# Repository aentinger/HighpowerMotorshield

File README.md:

💾 Highpower Motorshield
========================

# 📸 Image

# 📂 Description

The Highpower Motorshield facilitates the control of a highpower DC (direct current) motor (18 V / 46 A) with an Arduino. The shield also permits the measurement of the motor current. For a quick and easy start, an open source Arduino library with sample programs is available.

**Features**

* Control of a normal direct current motor
* Supply voltage range: 7 to 18 Volts
* Can be used with 2S, 3S and 4S LiPo-battery
* High performance: Maximum continuous output current: 46 A
* Motor drivers are protected against short circuiting (to ground/supply), overheating, overvoltage and undervoltage
* Current measurement of the motor current
* Arduino Library with example programs is available on GitHub

# 🎥 [Video](images/highpower_motorshield_demo.mp4)

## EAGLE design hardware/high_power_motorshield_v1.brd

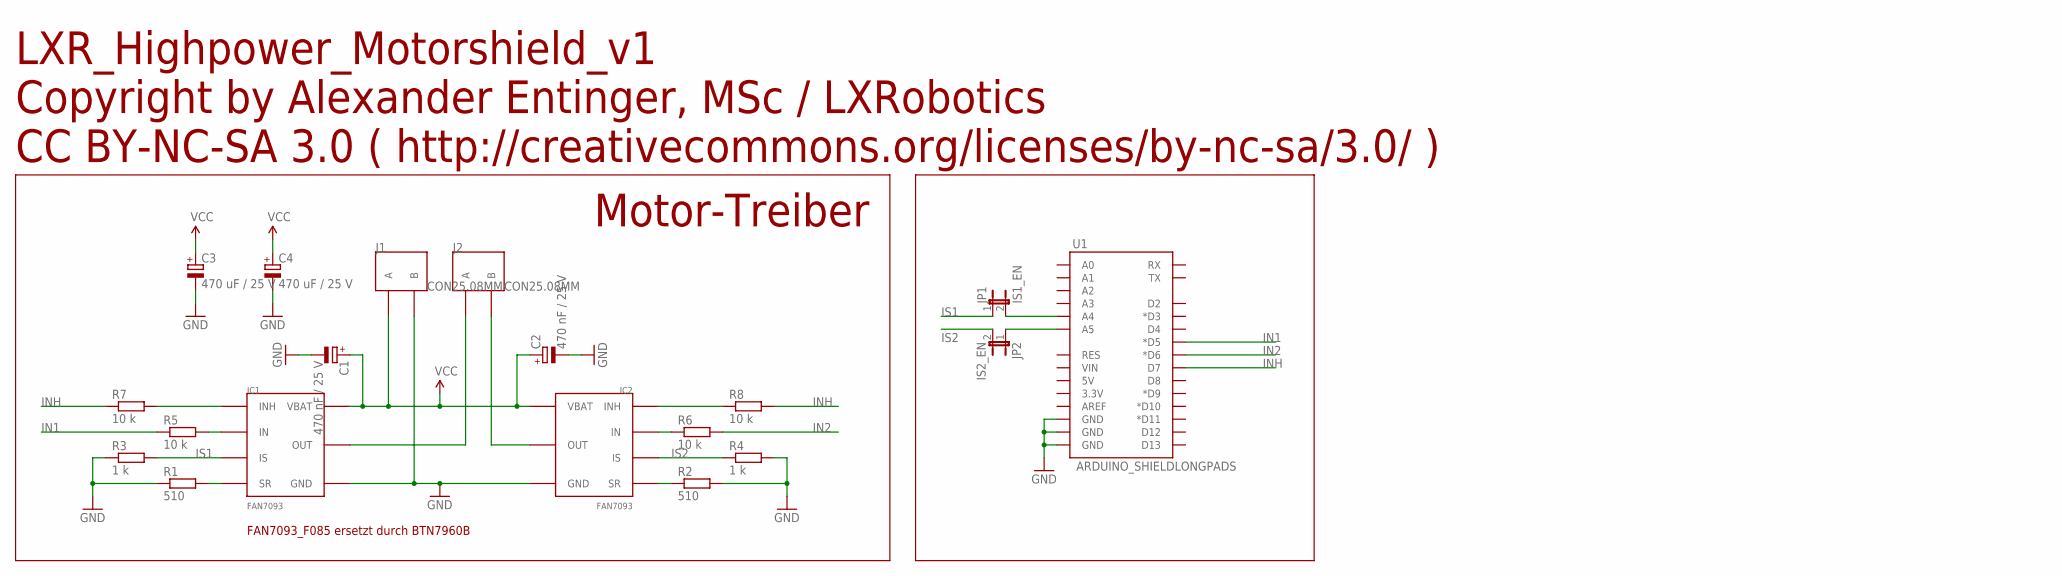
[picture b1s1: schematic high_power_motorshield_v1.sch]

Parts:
C1, C2: 470 nF / 25 V; KEMET_A
C3, C4: 470 uF / 25 V; E5-10,5
IC1, IC2: FAN7093; TO263-7L
J1, J2: CON25.08MM; CON2_SCHRAUBKLEMME
JP1: IS1_EN; JP1
JP2: IS2_EN; JP1
R1, R2: 510; R0805
R3, R4: 1 k; R0805
R5, R6, R7, R8: 10 k; R0805
U1: ARDUINO_SHIELDLONGPADS; DUEMILANOVE_SHIELD_LONGPADS

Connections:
GND: C1.CATHODE (-), C2.CATHODE (-), C3.-, C4.-, IC1.GND, IC2.GND, J1.2 (B), R1.1, R2.2, R3.1, R4.2, U1.GND@0 (GND), U1.GND@1 (GND), U1.GND@2 (GND)
IN1: R5.1, U1.D5 (*D5)
IN2: R6.2, U1.D6 (*D6)
INH: R7.1, R8.2, U1.D7
IS1: IC1.IS, JP1.1, R3.2
IS2: IC2.IS, JP2.2, R4.1
unnamed: IC1.INH, R7.2
unnamed: IC1.IN, R5.2
unnamed: IC1.OUT, IC1.OUT@1 (OUT), J2.1 (A)
unnamed: IC2.OUT, IC2.OUT@1 (OUT), J2.2 (B)
unnamed: JP1.2, U1.A4
unnamed: IC1.SR, R1.2
unnamed: IC2.SR, R2.1
unnamed: JP2.1, U1.A5
unnamed: IC2.IN, R6.1
unnamed: IC2.INH, R8.1
VCC: C1.ANODE (+), C2.ANODE (+), C3.+, C4.+, IC1.VBATT (VBAT), IC2.VBATT (VBAT), J1.1 (A)

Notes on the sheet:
LXR_Highpower_Motorshield_v1 Copyright by Alexander Entinger, MSc / LXRobotics CC BY-NC-SA 3.0 ( http://creativecommons.org/licenses/by-nc-sa/3.0/ )
Motor-Treiber
FAN7093_F085 ersetzt durch BTN7960B

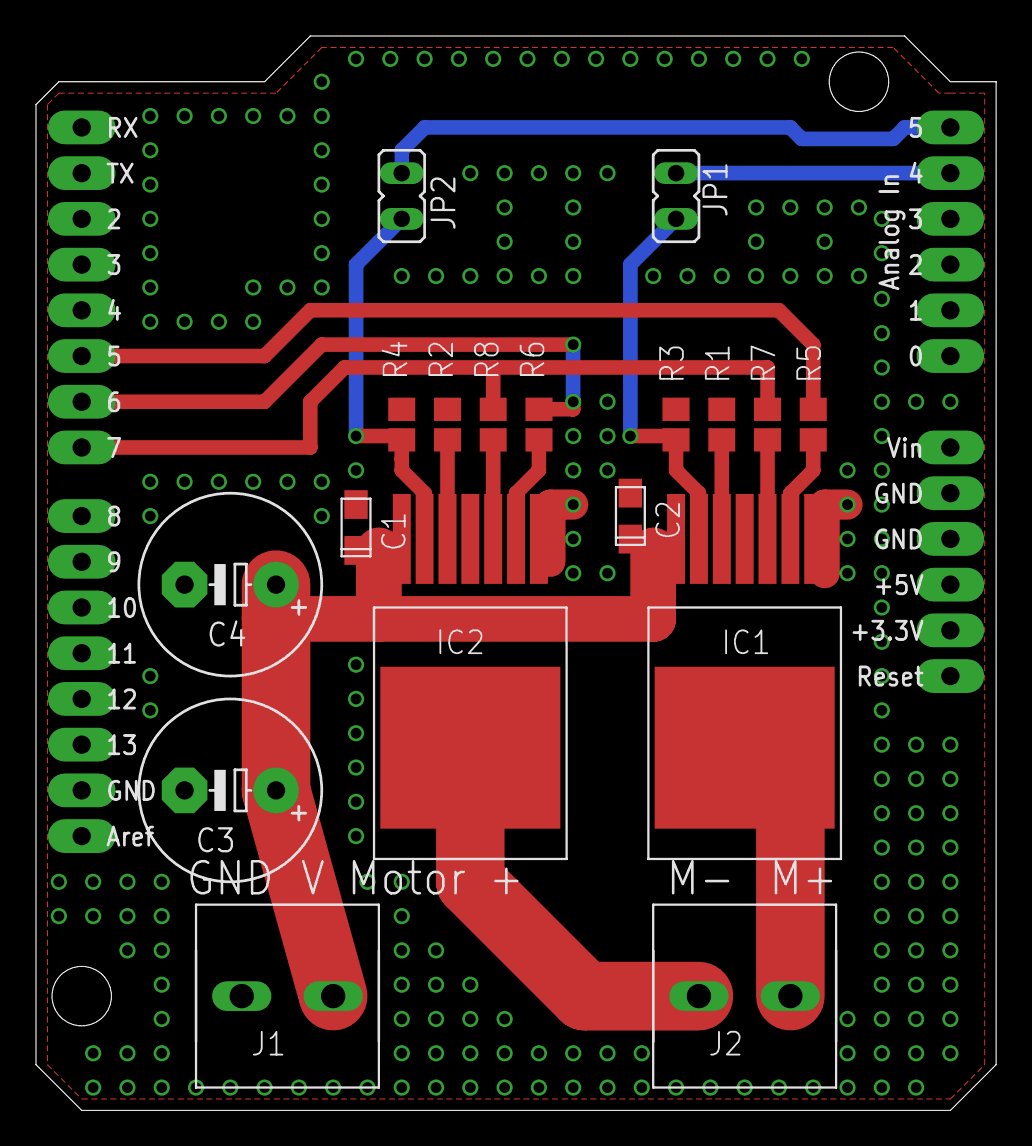
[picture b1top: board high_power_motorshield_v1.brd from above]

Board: 2 copper layers, 53.3 x 59.7 mm, 19 parts (0 on the bottom side), 17 nets.

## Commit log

2014-01-15 initial checkin of highpower motorshield
2014-01-16 adding software for driving motor via serial interface
2014-01-16 minor change in serial motor driver (activating timeout)
2014-04-30 adding featherweight electronic speed controller software
2014-05-05 adding latest version of featherweight electronic speed controller
2014-05-14 fine tuning of parameters
2014-05-14 Added Makefile for linux support
2014-08-20 FAN7093_F085 replaced with BTN7960B
2017-06-26 Adding hardware and images
2025-03-26 Add BOM.
2025-03-26 Add demo video.
2025-03-26 Pretty up README.

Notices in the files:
README.md:
License: CC BY-NC-SA 4.0
parts and their libraries:
SparkFun-Boards: Licensing: CC v3.0 Share-Alike You are welcome to use this library for commercial purposes.
